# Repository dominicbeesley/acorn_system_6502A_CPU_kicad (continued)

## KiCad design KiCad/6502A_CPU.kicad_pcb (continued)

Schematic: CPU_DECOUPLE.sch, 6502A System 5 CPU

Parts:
C1: 22u; CP_Axial_L10.0mm_D4.5mm_P15.00mm_Horizontal_tight
C4, C5, C6, C7: 47n; C_Disc_D3.0mm_W1.6mm_P2.50mm
C8: 47n; C_Disc_D3.0mm_W1.6mm_P2.50mm_tight
C9, C10, C11: 47n; C_Disc_D3.0mm_W1.6mm_P2.54mm_tight
IC1: 74S04; DIP-14_W7.62mm_Socket
IC5: 74LS74; DIP-14_W7.62mm_Socket
IC6, IC19: 74LS20; DIP-14_W7.62mm_Socket
IC14: 74LS04; DIP-14_W7.62mm_Socket
IC15: 74LS125; DIP-14_W7.62mm_Socket
IC16: 74LS86; DIP-14_W7.62mm_Socket
IC17: 74LS32; DIP-14_W7.62mm_Socket
IC18: 74LS132; DIP-14_W7.62mm_Socket
IC20: 74LS139

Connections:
GND: C1.2, C4.2, C5.2, C6.2, C7.2, C8.2, C9.2, C10.2, C11.2, IC1.7 (GND), IC5.7 (GND), IC6.7 (GND), IC14.7 (GND), IC15.7 (GND), IC16.7 (GND), IC17.7 (GND), IC18.7 (GND), IC19.7 (GND), IC20.8 (GND); also elsewhere on the board
VCC: C1.1, C4.1, C5.1, C6.1, C7.1, C8.1, C9.1, C10.1, C11.1, IC1.14 (VCC), IC5.14 (VCC), IC6.14 (VCC), IC14.14 (VCC), IC15.14 (VCC), IC16.14 (VCC), IC17.14 (VCC), IC18.14 (VCC), IC19.14 (VCC), IC20.16 (VCC); also elsewhere on the board

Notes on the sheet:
FIX: extra decouplers

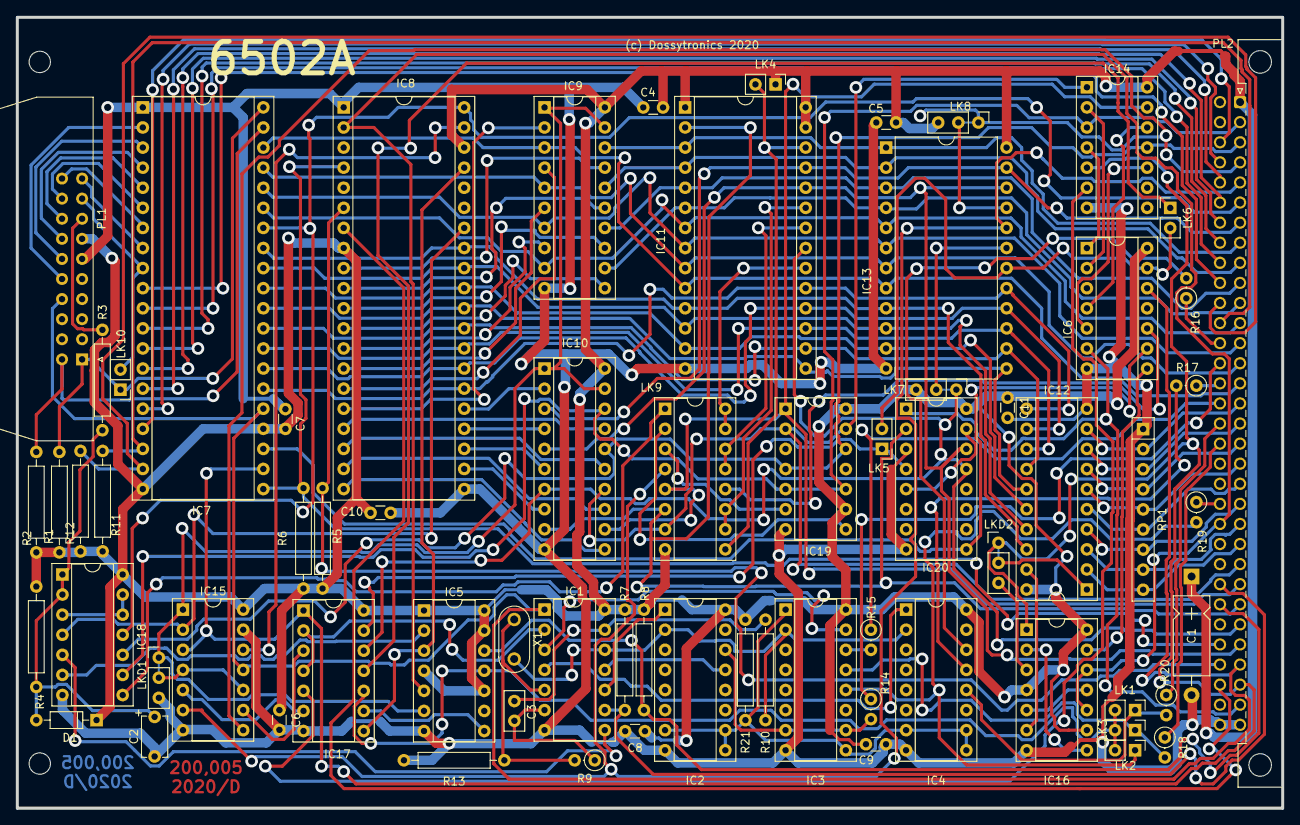
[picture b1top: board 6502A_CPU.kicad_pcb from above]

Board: 2 copper layers, 160.0 x 100.0 mm, 69 parts (0 on the bottom side), 146 nets.
